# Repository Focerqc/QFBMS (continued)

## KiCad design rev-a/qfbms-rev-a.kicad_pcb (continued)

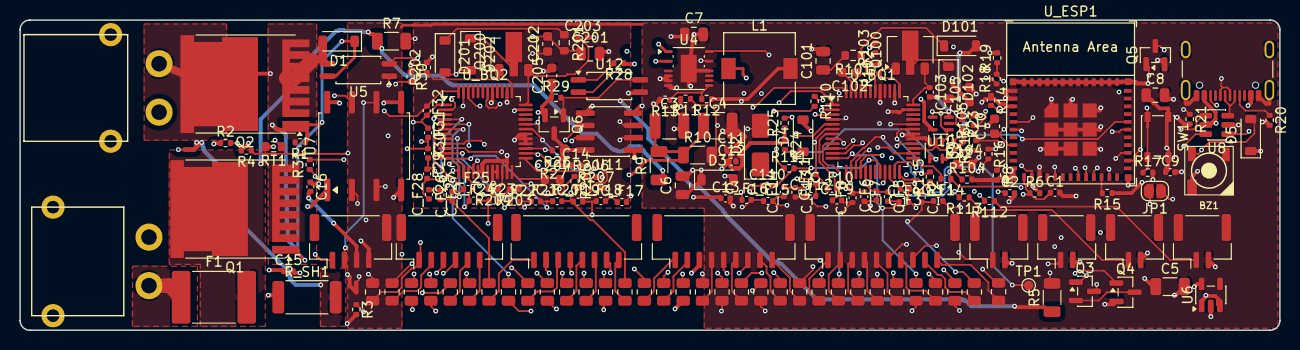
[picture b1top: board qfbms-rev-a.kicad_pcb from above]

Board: 4 copper layers, 130.0 x 32.0 mm, 193 parts (0 on the bottom side), 156 nets.

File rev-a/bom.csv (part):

Ref,Block,Value,MPN / requirement,Footprint,Fixed,Purpose
J_CELL1,cells,CELL9-CELL0,,Connector_JST:JST_GH_BM10B-GHS-TBT_1x10-1MP_P1.25mm_Vertical,yes,"Balance-lead plug, taps CELL9 down to CELL0 (fixed position)"
J_CELL2,cells,CELL18-CELL10,,Connector_JST:JST_GH_BM09B-GHS-TBT_1x09-1MP_P1.25mm_Vertical,yes,"Balance-lead plug, taps CELL18 down to CELL10 (fixed position)"
J_CELL3,cells,CELL26-CELL19,,Connector_JST:JST_GH_BM08B-GHS-TBT_1x08-1MP_P1.25mm_Vertical,yes,"Balance-lead plug, taps CELL26 down to CELL19 (fixed position)"
J_CELL4,cells,CELL32-CELL27,,Connector_JST:JST_GH_BM06B-GHS-TBT_1x06-1MP_P1.25mm_Vertical,yes,"Balance-lead plug, taps CELL32 down to CELL27 (fixed position)"
R_B33,cells,27R 0805,,Resistor_SMD:R_0805_2012Metric,yes,Cell-input / balance resistor for tap 0 (fixed position)
R_B32,cells,27R 0805,,Resistor_SMD:R_0805_2012Metric,yes,Cell-input / balance resistor for tap 1 (fixed position)
R_B31,cells,27R 0805,,Resistor_SMD:R_0805_2012Metric,yes,Cell-input / balance resistor for tap 2 (fixed position)
R_B30,cells,27R 0805,,Resistor_SMD:R_0805_2012Metric,yes,Cell-input / balance resistor for tap 3 (fixed position)
R_B29,cells,27R 0805,,Resistor_SMD:R_0805_2012Metric,yes,Cell-input / balance resistor for tap 4 (fixed position)
R_B28,cells,27R 0805,,Resistor_SMD:R_0805_2012Metric,yes,Cell-input / balance resistor for tap 5 (fixed position)
R_B27,cells,27R 0805,,Resistor_SMD:R_0805_2012Metric,yes,Cell-input / balance resistor for tap 6 (fixed position)
R_B26,cells,27R 0805,,Resistor_SMD:R_0805_2012Metric,yes,Cell-input / balance resistor for tap 7 (fixed position)
R_B25,cells,27R 0805,,Resistor_SMD:R_0805_2012Metric,yes,Cell-input / balance resistor for tap 8 (fixed position)
R_B24,cells,27R 0805,,Resistor_SMD:R_0805_2012Metric,yes,Cell-input / balance resistor for tap 9 (fixed position)
R_B23,cells,27R 0805,,Resistor_SMD:R_0805_2012Metric,yes,Cell-input / balance resistor for tap 10 (fixed position)
R_B22,cells,27R 0805,,Resistor_SMD:R_0805_2012Metric,yes,Cell-input / balance resistor for tap 11 (fixed position)
R_B21,cells,27R 0805,,Resistor_SMD:R_0805_2012Metric,yes,Cell-input / balance resistor for tap 12 (fixed position)
R_B20,cells,27R 0805,,Resistor_SMD:R_0805_2012Metric,yes,Cell-input / balance resistor for tap 13 (fixed position)
R_B19,cells,27R 0805,,Resistor_SMD:R_0805_2012Metric,yes,Cell-input / balance resistor for tap 14 (fixed position)
R_B18,cells,27R 0805,,Resistor_SMD:R_0805_2012Metric,yes,Cell-input / balance resistor for tap 15 (fixed position)
R_B17,cells,27R 0805,,Resistor_SMD:R_0805_2012Metric,yes,Cell-input / balance resistor for tap 16 (fixed position)
R_B16,cells,27R 0805,,Resistor_SMD:R_0805_2012Metric,yes,Cell-input / balance resistor for tap 17 (fixed position)
R_B15,cells,27R 0805,,Resistor_SMD:R_0805_2012Metric,yes,Cell-input / balance resistor for tap 18 (fixed position)
R_B14,cells,27R 0805,,Resistor_SMD:R_0805_2012Metric,yes,Cell-input / balance resistor for tap 19 (fixed position)
R_B13,cells,27R 0805,,Resistor_SMD:R_0805_2012Metric,yes,Cell-input / balance resistor for tap 20 (fixed position)
R_B12,cells,27R 0805,,Resistor_SMD:R_0805_2012Metric,yes,Cell-input / balance resistor for tap 21 (fixed position)
R_B11,cells,27R 0805,,Resistor_SMD:R_0805_2012Metric,yes,Cell-input / balance resistor for tap 22 (fixed position)
R_B10,cells,27R 0805,,Resistor_SMD:R_0805_2012Metric,yes,Cell-input / balance resistor for tap 23 (fixed position)
R_B9,cells,27R 0805,,Resistor_SMD:R_0805_2012Metric,yes,Cell-input / balance resistor for tap 24 (fixed position)
R_B8,cells,27R 0805,,Resistor_SMD:R_0805_2012Metric,yes,Cell-input / balance resistor for tap 25 (fixed position)
R_B7,cells,27R 0805,,Resistor_SMD:R_0805_2012Metric,yes,Cell-input / balance resistor for tap 26 (fixed position)
R_B6,cells,27R 0805,,Resistor_SMD:R_0805_2012Metric,yes,Cell-input / balance resistor for tap 27 (fixed position)
R_B5,cells,27R 0805,,Resistor_SMD:R_0805_2012Metric,yes,Cell-input / balance resistor for tap 28 (fixed position)
R_B4,cells,27R 0805,,Resistor_SMD:R_0805_2012Metric,yes,Cell-input / balance resistor for tap 29 (fixed position)
R_B3,cells,27R 0805,,Resistor_SMD:R_0805_2012Metric,yes,Cell-input / balance resistor for tap 30 (fixed position)
R_B2,cells,27R 0805,,Resistor_SMD:R_0805_2012Metric,yes,Cell-input / balance resistor for tap 31 (fixed position)
R_B1,cells,27R 0805,,Resistor_SMD:R_0805_2012Metric,yes,Cell-input / balance resistor for tap 32 (fixed position)
C_F1,cells,100n 16V,,Capacitor_SMD:C_0402_1005Metric,,Cell 1 input filter (with R_B) for the lower monitor
C_F2,cells,100n 16V,,Capacitor_SMD:C_0402_1005Metric,,Cell 2 input filter (with R_B) for the lower monitor
C_F3,cells,100n 16V,,Capacitor_SMD:C_0402_1005Metric,,Cell 3 input filter (with R_B) for the lower monitor
C_F4,cells,100n 16V,,Capacitor_SMD:C_0402_1005Metric,,Cell 4 input filter (with R_B) for the lower monitor
C_F5,cells,100n 16V,,Capacitor_SMD:C_0402_1005Metric,,Cell 5 input filter (with R_B) for the lower monitor
C_F6,cells,100n 16V,,Capacitor_SMD:C_0402_1005Metric,,Cell 6 input filter (with R_B) for the lower monitor
C_F7,cells,100n 16V,,Capacitor_SMD:C_0402_1005Metric,,Cell 7 input filter (with R_B) for the lower monitor
C_F8,cells,100n 16V,,Capacitor_SMD:C_0402_1005Metric,,Cell 8 input filter (with R_B) for the lower monitor
C_F9,cells,100n 16V,,Capacitor_SMD:C_0402_1005Metric,,Cell 9 input filter (with R_B) for the lower monitor
C_F10,cells,100n 16V,,Capacitor_SMD:C_0402_1005Metric,,Cell 10 input filter (with R_B) for the lower monitor
C_F11,cells,100n 16V,,Capacitor_SMD:C_0402_1005Metric,,Cell 11 input filter (with R_B) for the lower monitor
C_F12,cells,100n 16V,,Capacitor_SMD:C_0402_1005Metric,,Cell 12 input filter (with R_B) for the lower monitor
C_F13,cells,100n 16V,,Capacitor_SMD:C_0402_1005Metric,,Cell 13 input filter (with R_B) for the lower monitor
C_F14,cells,100n 16V,,Capacitor_SMD:C_0402_1005Metric,,Cell 14 input filter (with R_B) for the lower monitor
C_F15,cells,100n 16V,,Capacitor_SMD:C_0402_1005Metric,,Cell 15 input filter (with R_B) for the lower monitor
C_F16,cells,100n 16V,,Capacitor_SMD:C_0402_1005Metric,,Cell 16 input filter (with R_B) for the lower monitor
C_F17,cells,100n 16V,,Capacitor_SMD:C_0402_1005Metric,,Cell 17 input filter (with R_B) for the upper monitor
C_F18,cells,100n 16V,,Capacitor_SMD:C_0402_1005Metric,,Cell 18 input filter (with R_B) for the upper monitor
C_F19,cells,100n 16V,,Capacitor_SMD:C_0402_1005Metric,,Cell 19 input filter (with R_B) for the upper monitor
C_F20,cells,100n 16V,,Capacitor_SMD:C_0402_1005Metric,,Cell 20 input filter (with R_B) for the upper monitor
C_F21,cells,100n 16V,,Capacitor_SMD:C_0402_1005Metric,,Cell 21 input filter (with R_B) for the upper monitor
C_F22,cells,100n 16V,,Capacitor_SMD:C_0402_1005Metric,,Cell 22 input filter (with R_B) for the upper monitor
C_F23,cells,100n 16V,,Capacitor_SMD:C_0402_1005Metric,,Cell 23 input filter (with R_B) for the upper monitor
C_F24,cells,100n 16V,,Capacitor_SMD:C_0402_1005Metric,,Cell 24 input filter (with R_B) for the upper monitor
C_F25,cells,100n 16V,,Capacitor_SMD:C_0402_1005Metric,,Cell 25 input filter (with R_B) for the upper monitor
C_F26,cells,100n 16V,,Capacitor_SMD:C_0402_1005Metric,,Cell 26 input filter (with R_B) for the upper monitor
C_F27,cells,100n 16V,,Capacitor_SMD:C_0402_1005Metric,,Cell 27 input filter (with R_B) for the upper monitor
C_F28,cells,100n 16V,,Capacitor_SMD:C_0402_1005Metric,,Cell 28 input filter (with R_B) for the upper monitor
C_F29,cells,100n 16V,,Capacitor_SMD:C_0402_1005Metric,,Cell 29 input filter (with R_B) for the upper monitor
C_F30,cells,100n 16V,,Capacitor_SMD:C_0402_1005Metric,,Cell 30 input filter (with R_B) for the upper monitor
C_F31,cells,100n 16V,,Capacitor_SMD:C_0402_1005Metric,,Cell 31 input filter (with R_B) for the upper monitor
C_F32,cells,100n 16V,,Capacitor_SMD:C_0402_1005Metric,,Cell 32 input filter (with R_B) for the upper monitor
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
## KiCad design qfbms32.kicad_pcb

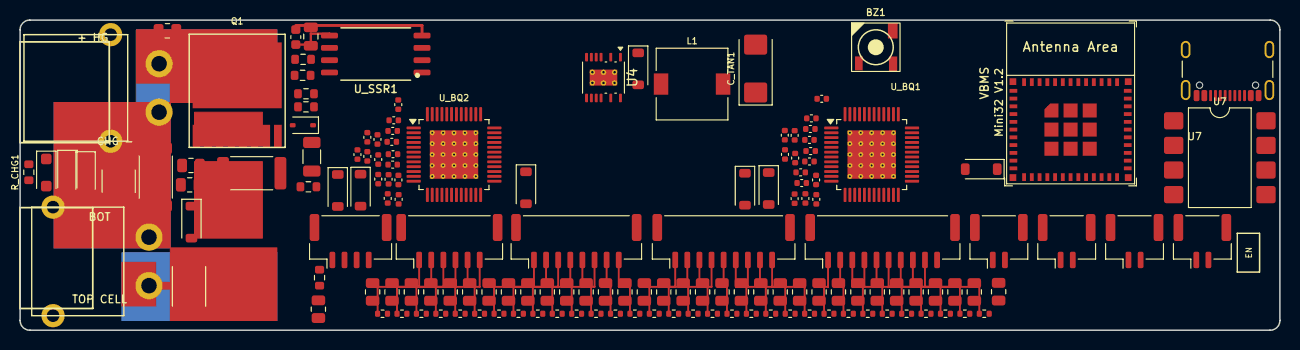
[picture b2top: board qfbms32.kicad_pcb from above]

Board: 2 copper layers, 130.0 x 32.0 mm, 149 parts (0 on the bottom side), 84 nets.

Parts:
BZ1: FUET-5030; Buzzer_5.0x5.0mm_SMD
C_DISC: 10uF; C_1206_3216Metric
C_F1, C_F2, C_F3, C_F4, C_F5, C_F6, C_F7, C_F8, C_F9, C_F10, C_F11, C_F12, C_F13, C_F14, C_F15, C_F16, C_F17, C_F18, C_F19, C_F20, C_F21, C_F22, C_F23, C_F24, C_F25, C_F26, C_F27, C_F28, C_F29, C_F30, C_F31, C_F32: 0.22uF; C_0402_1005Metric
C_FLT1: 10uF_100V; C_1812_4532Metric
C_SSR1: 100nF; C_0603_1608Metric
C_SSR2: 1uF; C_0805_2012Metric
C_TAN1: 100uF_16V; CP_EIA-6032-28_Kemet-C
D_BST1: Schottky; D_SOD-123
D_CHG1, D_CHG2, D_CHG3: DSK320; D_SOD-123F
D_GS1: PDZ16B; D_SOD-323
D_PRI1, D_PRI2, D_PRI3: D_Schottky; D_SOD-123
D_S1: TVS; D_SOD-123
D_SEC1, D_SEC2, D_SEC3: D_Schottky; D_SOD-123
F1: JT 15A; Fuse_2512_6332Metric
FB1: Unmarked; R_0603_1608Metric
J_BAT1: XT30PW-M (BAT); XT30PW-M_Lugs
J_CELL1: 0-8; JST_GH_BM10B-GHS-TBT_1x10-1MP_P1.25mm_Vertical
J_CELL2: 9-16; JST_GH_BM09B-GHS-TBT_1x09-1MP_P1.25mm_Vertical
J_CELL3: 17-24; JST_GH_BM08B-GHS-TBT_1x08-1MP_P1.25mm_Vertical
J_CELL4: 25-32; JST_GH_BM06B-GHS-TBT_1x06-1MP_P1.25mm_Vertical
J_CHG1: XT30PW-F (CHG); XT30PW-F_Lugs
J_COMM1: CAN/5V; JST_GH_BM04B-GHS-TBT_1x04-1MP_P1.25mm_Vertical
J_T1: T1; JST_GH_BM02B-GHS-TBT_1x02-1MP_P1.25mm_Vertical
J_T2: T2; JST_GH_BM02B-GHS-TBT_1x02-1MP_P1.25mm_Vertical
J_T3: T3; JST_GH_BM02B-GHS-TBT_1x02-1MP_P1.25mm_Vertical
J_T4: T4; JST_GH_BM02B-GHS-TBT_1x02-1MP_P1.25mm_Vertical
J_USB1: USB-C; USB_C_Receptacle_16P
L1: 180uH_181; L_7.3x7.3_H4.5
Q1: AGM15T03LL; TOLL-8_AGM15T03LL
R_B1, R_B2, R_B3, R_B4, R_B5, R_B6, R_B7, R_B8, R_B9, R_B10, R_B11, R_B12, R_B13, R_B14, R_B15, R_B16, R_B17, R_B18, R_B19, R_B20, R_B21, R_B22, R_B23, R_B24, R_B25, R_B26, R_B27, R_B28, R_B29, R_B30, R_B31, R_B32, R_B33: 27R0; R_0805_2012Metric
R_CHG1: 100k; R_0603_1608Metric
R_CHG2: 2203; R_0805_2012Metric
R_DSG1: 1000; R_0805_2012Metric
R_F1, R_F2, R_F3, R_F4, R_F5, R_F6, R_F7, R_F8, R_F9, R_F10, R_F11, R_F12, R_F13, R_F14, R_F15, R_F16, R_F17, R_F18, R_F19, R_F20, R_F21, R_F22, R_F23, R_F24, R_F25, R_F26, R_F27, R_F28, R_F29, R_F30, R_F31, R_F32: 20R; R_0402_1005Metric
R_G1: 01X; R_0603_1608Metric
R_GS1: 474; R_0603_1608Metric
R_S1, R_S2: 1000; R_0805_2012Metric
R_SEC1: 01X; R_0603_1608Metric
R_SH1, R_SH2: R001; R_2512_6332Metric
R_SSR1: 01X; R_0603_1608Metric
R_SSR2: 10k; R_0603_1608Metric
U4: LTC7138; Analog_MSOP-12-16-1EP_3x4.039mm_P0.5mm_EP1.651x2.845mm_Ther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
U7: ISO1050 (DUB-8); SMDIP-8_W9.53mm
U_BQ1: BQ7695202 (IC1); TQFP-48-1EP_7x7mm_P0.5mm_EP5x5mm_ThermalVias
U_BQ2: BQ7695202 (IC2); TQFP-48-1EP_7x7mm_P0.5mm_EP5x5mm_ThermalVias
U_ESP1: ESP32-C3-MINI-1
U_SSR1: GSRELAY; H2440_SSR

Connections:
5VExt: J_COMM1.4, U7.8
+3V3: BZ1.1, U7.1
BQ1_VC1: C_F1.1, C_F2.2, R_F32.2, U_BQ1.15
BQ1_VC2: C_F2.1, C_F3.2, R_F31.2, U_BQ1.14
BQ1_VC3: C_F3.1, C_F4.2, R_F30.2, U_BQ1.13
BQ1_VC4: C_F4.1, C_F5.2, R_F29.2, U_BQ1.12
BQ1_VC5: C_F5.1, C_F6.2, R_F28.2, U_BQ1.11
BQ1_VC6: C_F6.1, C_F7.2, R_F27.2, U_BQ1.10
BQ1_VC7: C_F7.1, C_F8.2, R_F26.2, U_BQ1.9
BQ1_VC8: C_F8.1, C_F9.2, R_F25.2, U_BQ1.8
BQ1_VC9: C_F9.1, C_F10.2, R_F24.2, U_BQ1.7
BQ1_VC10: C_F10.1, C_F11.2, R_F23.2, U_BQ1.6
BQ1_VC11: C_F11.1, C_F12.2, R_F22.2, U_BQ1.5
BQ1_VC12: C_F12.1, C_F13.2, R_F21.2, U_BQ1.4
BQ1_VC13: C_F13.1, C_F14.2, R_F20.2, U_BQ1.3
BQ1_VC14: C_F14.1, C_F15.2, R_F19.2, U_BQ1.2
BQ1_VC15: C_F15.1, C_F16.2, R_F18.2, U_BQ1.1
BQ1_VC16: C_F16.1, R_F17.2, U_BQ1.48
BQ2_VC1: C_F17.1, C_F18.2, R_F16.2, U_BQ2.15
BQ2_VC2: C_F18.1, C_F19.2, R_F15.2, U_BQ2.14
BQ2_VC3: C_F19.1, C_F20.2, R_F14.2, U_BQ2.13
BQ2_VC4: C_F20.1, C_F21.2, R_F13.2, U_BQ2.12
BQ2_VC5: C_F21.1, C_F22.2, R_F12.2, U_BQ2.11
BQ2_VC6: C_F22.1, C_F23.2, R_F11.2, U_BQ2.10
BQ2_VC7: C_F23.1, C_F24.2, R_F10.2, U_BQ2.9
BQ2_VC8: C_F24.1, C_F25.2, R_F9.2, U_BQ2.8
BQ2_VC9: C_F25.1, C_F26.2, R_F8.2, U_BQ2.7
BQ2_VC10: C_F26.1, C_F27.2, R_F7.2, U_BQ2.6
BQ2_VC11: C_F27.1, C_F28.2, R_F6.2, U_BQ2.5
BQ2_VC12: C_F28.1, C_F29.2, R_F5.2, U_BQ2.4
BQ2_VC13: C_F29.1, C_F30.2, R_F4.2, U_BQ2.3
BQ2_VC14: C_F30.1, C_F31.2, R_F3.2, U_BQ2.2
BQ2_VC15: C_F31.1, C_F32.2, R_F2.2, U_BQ2.1
BQ2_VC16: C_F32.1, R_F1.2, U_BQ2.48
CANH: J_COMM1.1, U7.7
CANL: J_COMM1.2, U7.6
CELL0: C_F1.2, J_BAT1.2, J_CELL1.10, R_SH1.1, U_BQ1.16
CELL1: J_CELL1.9, R_F32.1
CELL2: J_CELL1.8, R_F31.1
CELL3: J_CELL1.7, R_F30.1
CELL4: J_CELL1.6, R_F29.1
CELL5: J_CELL1.5, R_F28.1
CELL6: J_CELL1.4, R_F27.1
CELL7: J_CELL1.3, R_F26.1
CELL8: J_CELL1.2, R_F25.1
CELL9: J_CELL1.1, R_F24.1
CELL10: J_CELL2.9, R_F23.1
CELL11: J_CELL2.8, R_F22.1
CELL12: J_CELL2.7, R_F21.1
CELL13: J_CELL2.6, R_F20.1
CELL14: J_CELL2.5, R_F19.1
CELL15: J_CELL2.4, R_F18.1
CELL16: C_F17.2, J_CELL2.3, R_F17.1, U_BQ2.16
CELL17: J_CELL2.2, R_F16.1
CELL18: J_CELL2.1, R_F15.1
CELL19: J_CELL3.8, R_F14.1
CELL20: J_CELL3.7, R_F13.1
CELL21: J_CELL3.6, R_F12.1
CELL22: J_CELL3.5, R_F11.1
CELL23: J_CELL3.4, R_F10.1
CELL24: J_CELL3.3, R_F9.1
CELL25: J_CELL3.2, R_F8.1
CELL26: J_CELL3.1, R_F7.1
CELL27: J_CELL4.6, R_F6.1
CELL28: J_CELL4.5, R_F5.1
CELL29: J_CELL4.4, R_F4.1
CELL30: J_CELL4.3, R_F3.1
CELL31: J_CELL4.2, R_F2.1
CELL32: F1.1, J_BAT1.1, J_CELL4.1, R_F1.1, U_SSR1.6
CELL32_FUSED: F1.2, Q1.D
CHG+: D_GS1.2, J_CHG1.1, Q1.2, Q1.3, Q1.4, Q1.5, Q1.6, Q1.7, Q1.8, R_GS1.2
CHG-: J_CHG1.2, R_SH2.2
GND: C_SSR1.2, C_SSR2.2, J_T1.2, J_T2.2, J_T3.2, J_T4.2, R_SSR2.2, U7.4, U_BQ1.17, U_BQ2.17, U_SSR1.4
ISO_GND: J_COMM1.3, U7.5
Q1_GATE: D_GS1.1, Q1.1, R_G1.1, R_GS1.1, R_SSR1.2, R_SSR2.1
SHUNT_MID: R_SH1.2, R_SH2.1
SRN: U_BQ1.20, U_BQ2.20
SRP: U_BQ1.18, U_BQ2.18
SSR_OUT_CHG: R_G1.2, R_SSR1.1
TS1: J_T1.1, U_BQ1.21
TS2: J_T2.1, U_BQ1.22
TS3: J_T3.1, U_BQ1.23
TS4: J_T4.1, U_BQ2.21
VBOOST: C_SSR1.1, C_SSR2.1, U_SSR1.5

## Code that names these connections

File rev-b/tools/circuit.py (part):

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cell_connector = next(p for p in PARTS if p["ref"] == "J_CELL1")
del cell_connector["pins"]["10"]
cell_connector["nc"].append("10")
cell_connector["purpose"] += "; pin 10 CELL0 wire unused in rev B (main BAT- required)"
R("R208", "27R 0805", "CELL16", "VC0_BQ2",
  "Dedicated upper VC0 return; never share lower VC16 balancing current", "upper", fp=FP_R0805)
C("C106", "100n 16V", "TAP0_F", "GND", "Local VC0-VSS capacitor, TI table 16-3", "lower", fp=FP_C0603)
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     "Gate clamp, keeps transients under the FETs' +-20 V gate rating", "charge", mpn="BZT52C12")
R("R2", "120R", "3V3", "LED_A", "Sets ~15 mA through the VOM1271 LED", "charge")
part("Q3", "Transistor_FET:Q_NMOS_GSD", "AO3400A", FP_SOT23, {"1": "CHG_EN", "2": "LED_MID", "3": "LED_K"},
     "LED switch 1: on when firmware sets CHG_EN (GPIO5)", "charge", mpn="AO3400A")
part("Q4", "Transistor_FET:Q_NMOS_GSD", "AO3400A", FP_SOT23, {"1": "PSW_EN", "2": "LED_WD", "3": "LED_MID"},
     "LED switch 2: firmware raises PSW_EN (GPIO10) before any switch; both must be on", "charge",
     mpn="AO3400A")
R("R3", "100k", "CHG_EN", "GND", "Keeps CHG_EN low while the ESP32 resets", "charge")
R("R4", "100k", "PSW_EN", "GND", "Keeps PSW_EN low while the ESP32 resets", "charge")
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part("L1", "Device:L", "180uH >=0.7A", "Inductor_SMD:L_7.3x7.3_H4.5", {"1": "SW", "2": "5V_BUCK"},
     "Buck inductor (VBMS uses 180 uH)", "power", mpn="180 uH shielded 7.3x7.3, Isat >= 0.7 A")
part("D2", "Device:D", "ES1D", FP_SMA, {"1": "SW", "2": "ANODE"},
     "Buck catch diode; anode returns through the ANODE sense pin", "power", mpn="ES1D")
R("R12", "1.05M 1%", "5V_BUCK", "VFB", "Feedback top: 0.8 V x (1 + 1.05M/200k) = 5.0 V", "power")
R("R13", "200k 1%", "VFB", "GND", "Feedback bottom", "power")
C("C5", "22u 10V", "5V_BUCK", "GND", "Buck output capacitor", "power", fp=FP_C1206)
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part("U_ESP1", "qfbms_revb:ESP32-C3-MINI-1", "ESP32-C3-MINI-1", "qfbms_revb:ESP32-C3-MINI-1",
     {"1": "GND", "3": "3V3", "8": "EN", "12": "VCHG_ADC", "13": "VOUT_ADC", "5": "BTN",
      "6": "BUZ", "18": "CHG_HEARTBEAT", "19": "CHG_EN", "16": "PSW_EN", "20": "CAN_RX", "21": "CAN_TX",
      "22": "GPIO8", "23": "COM_EN", "26": "USB_DN", "27": "USB_DP", "30": "SCL", "31": "SDA"},
     "Runs VESC Express VBMS32 firmware and the Micro package (pins per hw_vbms32.h)", "mcu",
     mpn="ESP32-C3-MINI-1-N4")
C("C8", "10u 10V", "3V3", "GND", "ESP32 bulk decoupling", "mcu", fp=FP_C0805)
C("C9", "100n", "3V3", "GND", "ESP32 HF decoupling", "mcu")
R("R14", "10k", "3V3", "EN", "EN RC delay, R (Espressif: 10k/1uF)", "mcu")
C("C10", "1u", "EN", "GND", "EN RC delay, C", "mcu", fp=FP_C0603)
R("R15", "10k", "3V3", "GPIO8", "GPIO8 strap high (needed for download boot); PCHG_EN is unused", "mcu")
R("R16", "10k", "3V3", "COM_EN", "GPIO9 strap high = normal boot; also keeps the upper link off at reset", "mcu")
part("TP1", "Connector:TestPoint", "BOOT", "TestPoint:TestPoint_Pad_D1.0mm", {"1": "COM_EN"},
     "Short to GND at power-up for manual download mode", "mcu")
R("R17", "100k", "BTN", "GND", "ENABLE input idles low = 'key off' (firmware: high keeps it awake)", "mcu")
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for ref, a, b, what in [("U9", "SDA", "SDA_ISO1", "SDA"), ("U10", "SCL", "SCL_ISO1", "SCL")]:
    part(ref, "74xGxx:74CBTLV1G125", "74CBTLV1G125", "Package_TO_SOT_SMD:SOT-353_SC-70-5",
         {"1": "COM_EN", "2": a, "4": b, "3": "GND", "5": "3V3"},
         f"Bus switch ({what}): hides the upper monitor while COM_EN (GPIO9) is high, "
         "as the firmware's address-change startup needs", "comms", mpn="SN74CBTLV1G125DCKR")
C("C11", "100n", "3V3", "GND", "U9 decoupling", "comms")
C("C12", "100n", "3V3", "GND", "U10 decoupling", "comms")
part("U11", "Isolator:ISO1540", "ISO1640BDR", "Package_SO:SOIC-8_3.9x4.9mm_P1.27mm",
     {"1": "3V3", "2": "SDA_ISO1", "3": "SCL_ISO1", "4": "GND", "5": "CELL16", "6": "SCL_BQ2",
      "7": "SDA_BQ2", "8": "ISO_VCC2"},
     "I2C isolator to the upper monitor (CELL16 domain); ISO1640 = ISO1540 pinout", "comms",
     mpn="ISO1640BDR")
C("C13", "100n", "3V3", "GND", "ISO1640 side-1 decoupling", "comms")
C("C14", "100n", "ISO_VCC2", "CELL16", "ISO1640 side-2 decoupling", "comms")
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R("R27", "4.7k", "ISO_VCC2", "SCL_BQ2", "Upper-monitor bus pull-up (SCL)", "comms")
# Isolator side 2 runs from the upper monitor's REG1 only while COM_EN is low,
# so the top 16 cells are not drained by the isolator during deep sleep.
part("U12", "Isolator:PC817", "VOMA617A", FP_SOP4, {"1": "COM_LED_A", "2": "COM_EN", "4": "ISO_PG", "3": "CELL16"},
     "Opto: COM_EN low turns on the isolator's upper-side supply", "comms", mpn="VOMA617A-3X001T")
R("R28", "1k", "3V3", "COM_LED_A", "Opto LED current, ~2 mA (sunk by GPIO9 low)", "comms")
part("Q6", "Transistor_FET:Q_PMOS_GSD", "AO3401A", FP_SOT23, {"1": "ISO_PG", "2": "REG1_BQ2", "3": "ISO_VCC2"},
     "Switches upper REG1 to the isolator side 2", "comms", mpn="AO3401A")
R("R29", "100k", "REG1_BQ2", "ISO_PG", "Holds Q6 off unless the opto pulls its gate", "comms")
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
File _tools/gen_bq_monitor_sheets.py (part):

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        ref_ic = "U_BQ2"
        vss = "CELL16"
        title = "QFBMS32 upper monitor U_BQ2"
        cell0 = 16
        rbase = 101
        cbase = 101
        dbase = 101
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        ref_ic = "U_BQ1"
        vss = "CELL0"
        title = "QFBMS32 lower monitor U_BQ1"
        cell0 = 0
        rbase = 1
        cbase = 1
        dbase = 1
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        g = pwr_gnd(net,(iso[num][0]+dx,iso[num][1]))
        sch.wire(iso[num],g)
    sch.text((201,128),"OPEN   Select ISO1640 orderable 8-D suffix. Check rail margins and sequencing.",1.4)
    alert = sch.label("ALERT_BQ2",(332,154),180,"hier","bidirectional")
    end = (alert[0]+10.16,alert[1])
    sch.wire(alert,end)
    sch.noconn(end)
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        device(ref,"Device:C" if cap else "Device:R",value,x,85,
               [net,"REG1_BQ1" if ref=="C205" else "HOST_3V3"],FP_C0603 if cap else FP_R0603)
    sch.text((22,119),"02   Bench host power",2.5)
    device("J201","Connector:Conn_01x02_Pin","External 3.3 V",48,153,["AUX_3V3","CELL0"])
    device("SW201","Switch:SW_SPST","Host run",140,153,["AUX_3V3","HOST_3V3"])
    sch.text((22,173),"Close SW201 to start the host with both REG1 rails off.\nProduction auxiliary supply, protection and hold-up OPEN.",1.65)
    sch.text((214,119),"03   Manual wake  /  host power must be valid",2.5)
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    device("R208","Device:R","47k",259,207,["WAKE_BASE","CELL0"],FP_R0603,90)
    device("Q201","Transistor_BJT:Q_NPN_BEC","BC847BTT1G",343,185,["WAKE_BASE","CELL0","TS2_WAKE_BQ1"])
    device("R209","Device:R","249R",259,231,["WAKE_PULSE","LED_A"],FP_R0603,90)
    device("U207","Isolator:PC817","VOMA617A-3X001T",343,231,["LED_A","CELL0","CELL16","TS2_WAKE_BQ2"])
    sch.text((22,207),"SW202 owns both wake paths. Release before requesting SHUTDOWN.\nNo ESP output drives the base or LED. Hot released leakage OPEN.",1.65)
    return sch

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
